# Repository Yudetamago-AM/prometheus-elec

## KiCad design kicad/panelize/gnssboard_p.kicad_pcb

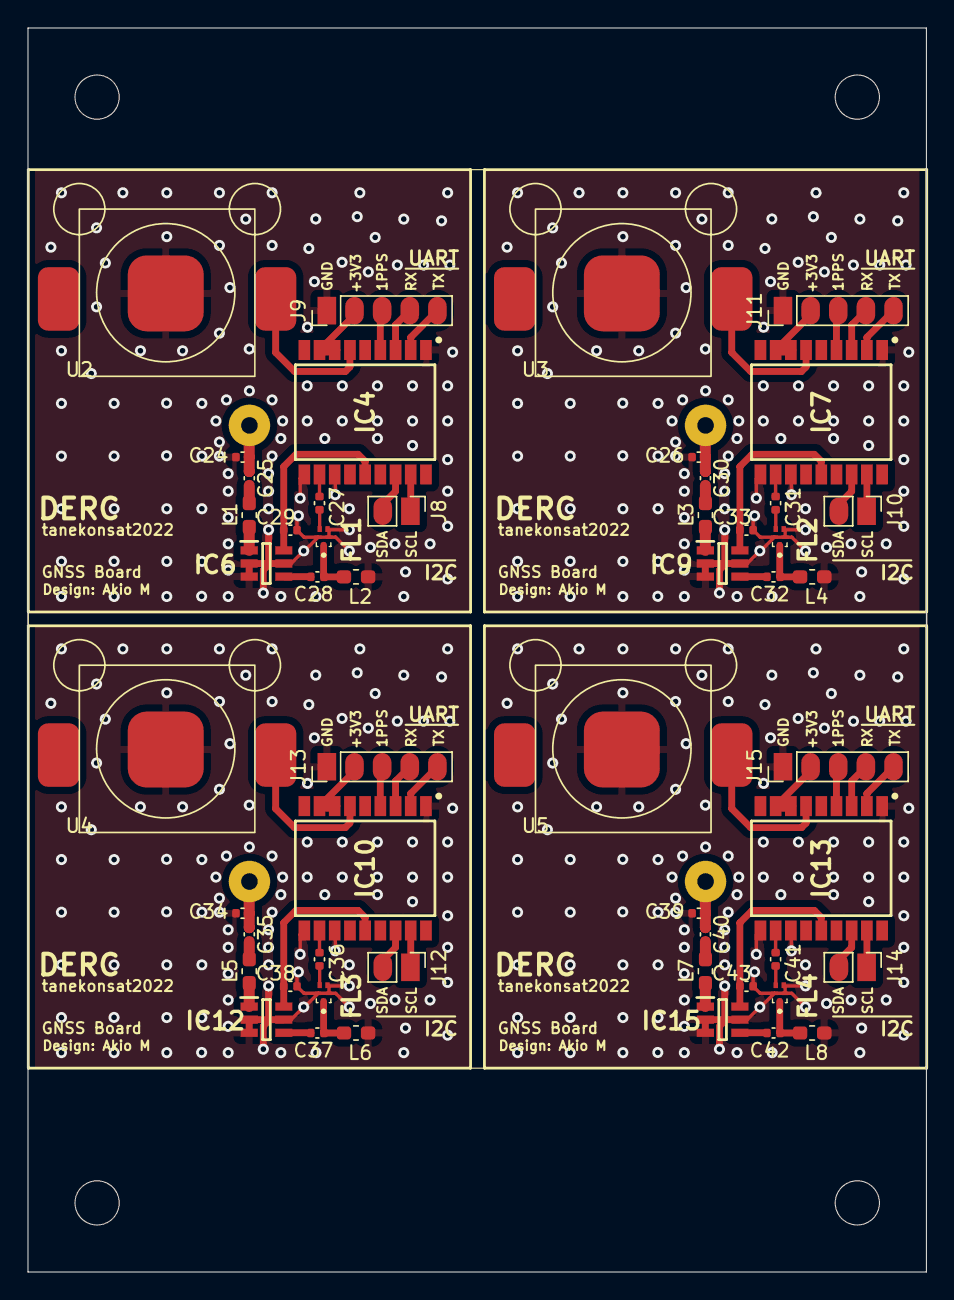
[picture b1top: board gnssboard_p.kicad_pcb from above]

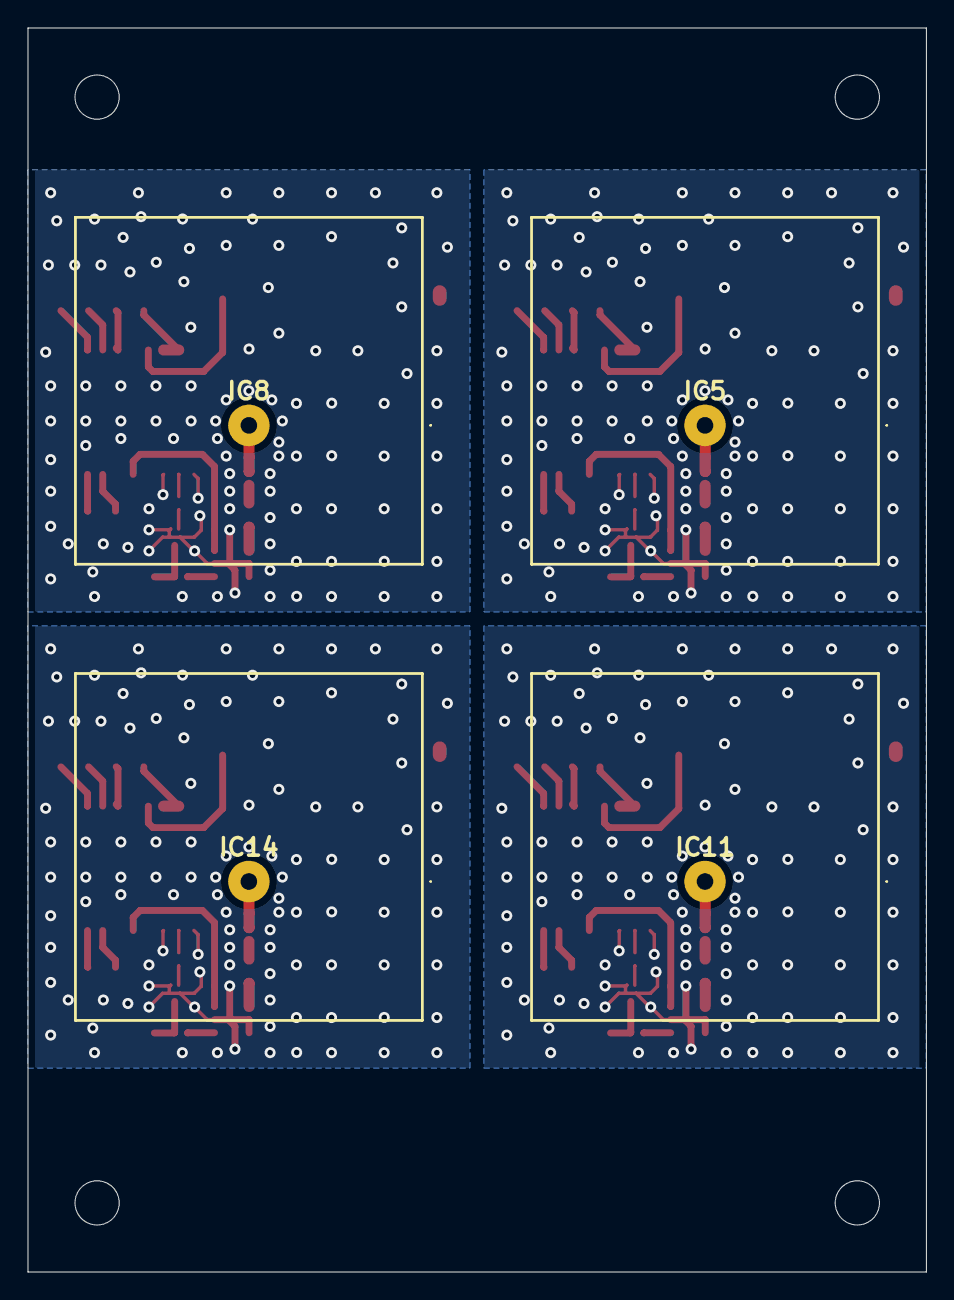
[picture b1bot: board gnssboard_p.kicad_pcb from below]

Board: 2 copper layers, 65.0 x 90.0 mm, 56 parts (4 on the bottom side), 16 nets.

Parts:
C24, C26, C34, C39: 1p; C_0402_1005Metric
C25, C28, C30, C32, C35, C37, C40, C42: 100p; C_0402_1005Metric
C27, C31, C36, C41: 120p; C_0402_1005Metric
C29, C33, C38, C43: 470p; C_0402_1005Metric
FL1, FL2, FL3, FL4: SAFEA1G58KA0F00R15
IC4, IC7, IC10, IC13: TESEO-LIV3F; SON110P970X1010X230-18N
IC5, IC8, IC11, IC14: CGGBPD.25.A; CGGBPD25A
IC6, IC9, IC12, IC15: MAX2641EUT+T; SOT95P280X145-6N
J8, J10, J12, J14: Conn_01x02_Female; PinHeader_1x02_P2.00mm_Vertical
J9, J11, J13, J15: Conn_01x05_Female; PinHeader_1x05_P2.00mm_Vertical
L1, L3, L5, L7: 5.6n; L_0603_1608Metric_Pad1.05x0.95mm_HandSolder
L2, L4, L6, L8: 6.8n; L_0603_1608Metric_Pad1.05x0.95mm_HandSolder
U2, U3, U4, U5: CR1025; CR1025_Holder

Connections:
+3V0: IC4.6 (VBATT), IC7.6 (VBATT), IC10.6 (VBATT), IC13.6 (VBATT), U2.2 (plus), U3.2 (plus), U4.2 (plus), U5.2 (plus)
+3V3: IC4.7 (VCC_IO), IC4.8 (VCC), IC7.7 (VCC_IO), IC7.8 (VCC), IC10.7 (VCC_IO), IC10.8 (VCC), IC13.7 (VCC_IO), IC13.8 (VCC), J9.2, J11.2, J13.2, J15.2
/GNSS_1PPS: IC4.4 (1PPS), IC7.4 (1PPS), IC10.4 (1PPS), IC13.4 (1PPS), J9.3, J11.3, J13.3, J15.3
/GPIO4_GNSS_RX: IC4.3 (RX), IC7.3 (RX), IC10.3 (RX), IC13.3 (RX), J9.4, J11.4, J13.4, J15.4
/GPIO5_GNSS_TX: IC4.2 (TX), IC7.2 (TX), IC10.2 (TX), IC13.2 (TX), J9.5, J11.5, J13.5, J15.5
/VCC_RF: C29.1, C33.1, C38.1, C43.1, IC4.14 (VCC_RF), IC6.6 (VCC), IC7.14 (VCC_RF), IC9.6 (VCC), IC10.14 (VCC_RF), IC12.6 (VCC), IC13.14 (VCC_RF), IC15.6 (VCC)
GND2: C24.2, C26.2, C29.2, C33.2, C34.2, C38.2, C39.2, C43.2, FL1.2 (GND_1), FL1.3 (GND_2), FL1.5 (GND_3), FL2.2 (GND_1), FL2.3 (GND_2), FL2.5 (GND_3), FL3.2 (GND_1), FL3.3 (GND_2), FL3.5 (GND_3), FL4.2 (GND_1), FL4.3 (GND_2), FL4.5 (GND_3), IC4.1 (GND), IC4.10 (GND_RF_1), IC4.12 (GND_RF_2), IC6.2 (GND_1), IC6.3 (GND_2), IC6.5 (GND_3), IC7.1 (GND), IC7.10 (GND_RF_1), IC7.12 (GND_RF_2), IC9.2 (GND_1), IC9.3 (GND_2), IC9.5 (GND_3), IC10.1 (GND), IC10.10 (GND_RF_1), IC10.12 (GND_RF_2), IC12.2 (GND_1), IC12.3 (GND_2), IC12.5 (GND_3), IC13.1 (GND), IC13.10 (GND_RF_1), IC13.12 (GND_RF_2), IC15.2 (GND_1), IC15.3 (GND_2), IC15.5 (GND_3), J9.1, J11.1, J13.1, J15.1, L2.2, L4.2, L6.2, L8.2, U2.1 (minus), U3.1 (minus), U4.1 (minus), U5.1 (minus)
unnamed: C24.1, C25.1, C26.1, C30.1, C34.1, C35.1, C39.1, C40.1, IC5.1, IC8.1, IC11.1, IC14.1
unnamed: C25.2, C30.2, C35.2, C40.2, L1.1, L3.1, L5.1, L7.1
unnamed: C27.1, C31.1, C36.1, C41.1, FL1.4 (OUT), FL2.4 (OUT), FL3.4 (OUT), FL4.4 (OUT)
unnamed: C27.2, C31.2, C36.2, C41.2, IC4.11 (RF_IN), IC7.11 (RF_IN), IC10.11 (RF_IN), IC13.11 (RF_IN)
unnamed: C28.1, C32.1, C37.1, C42.1, IC6.4 (RFOUT), IC9.4 (RFOUT), IC12.4 (RFOUT), IC15.4 (RFOUT)
unnamed: C28.2, C32.2, C37.2, C42.2, FL1.1 (IN), FL2.1 (IN), FL3.1 (IN), FL4.1 (IN), L2.1, L4.1, L6.1, L8.1
unnamed: IC4.16 (SDA), IC7.16 (SDA), IC10.16 (SDA), IC13.16 (SDA), J8.2, J10.2, J12.2, J14.2
unnamed: IC4.17 (SCL), IC7.17 (SCL), IC10.17 (SCL), IC13.17 (SCL), J8.1, J10.1, J12.1, J14.1
unnamed: IC6.1 (RFIN), IC9.1 (RFIN), IC12.1 (RFIN), IC15.1 (RFIN), L1.2, L3.2, L5.2, L7.2
